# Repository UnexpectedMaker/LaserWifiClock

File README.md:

# Mod-able Laser Wifi Clock
Design files and code for my open source Mod-able RGB Laser Wifi Clock that I sell on tindie:
https://www.tindie.com/products/15501/

It's custom hardware and custom code but all open source so if you want the challenge of making one yourself or you want to hack the code, go for it!

I have a live stream build of the board here if you want to see what's involved:
https://www.youtube.com/watch?v=2W7_SHC2Mis

# Design Files
Inlcluded in this reposity:
- EagleCAD schematics and Board layout files (Eagle 9.2) 
- Exported Gerber files (Gerber 274X)
- STL & DXF files for the 3D printed case and laser cut pieces
- Adrduino code

# Assembling the case
Here is a video guide to assembling the case

https://youtu.be/fARj-D6XGP0

# Hacking the code
You will need to have the ESP8266 board for Arduino IDE installed. If you don't, you can follow the instructions here:
https://arduino-esp8266.readthedocs.io/en/2.5.0-beta2/installing.html

Once installed you'll need to select the *LOLIN(WEMOS) D1 R2 & Mini* as the board type.

Plus the following libraries from Library Manager
- One Button
- TimeLib
- WifiManager (tzapu)
- ArduinoJson

Enjoy!

# Support Unexpected Maker

I love designing, making and releasing our projects as open source. I do it because I believe it’s important to share knowledge and give back to the community, like many have done before me. It helps us all learn and grow.

That said, a lot of time, effort and finances have gone into designing and releasing these files, so please consider supporting me by buy some of my TiinyPICO products:

https://tinypico.com/shop

Or by buying one of our products on tindie:

https://www.tindie.com/stores/seonr/

Or by becoming a Patron:

https://www.patreon.com/unexpectedmaker

# Unexpected Maker
http://youtube.com/c/unexpectedmaker

http://twitter.com/unexpectedmaker

https://www.facebook.com/unexpectedmaker/

https://www.instagram.com/unexpectedmaker/

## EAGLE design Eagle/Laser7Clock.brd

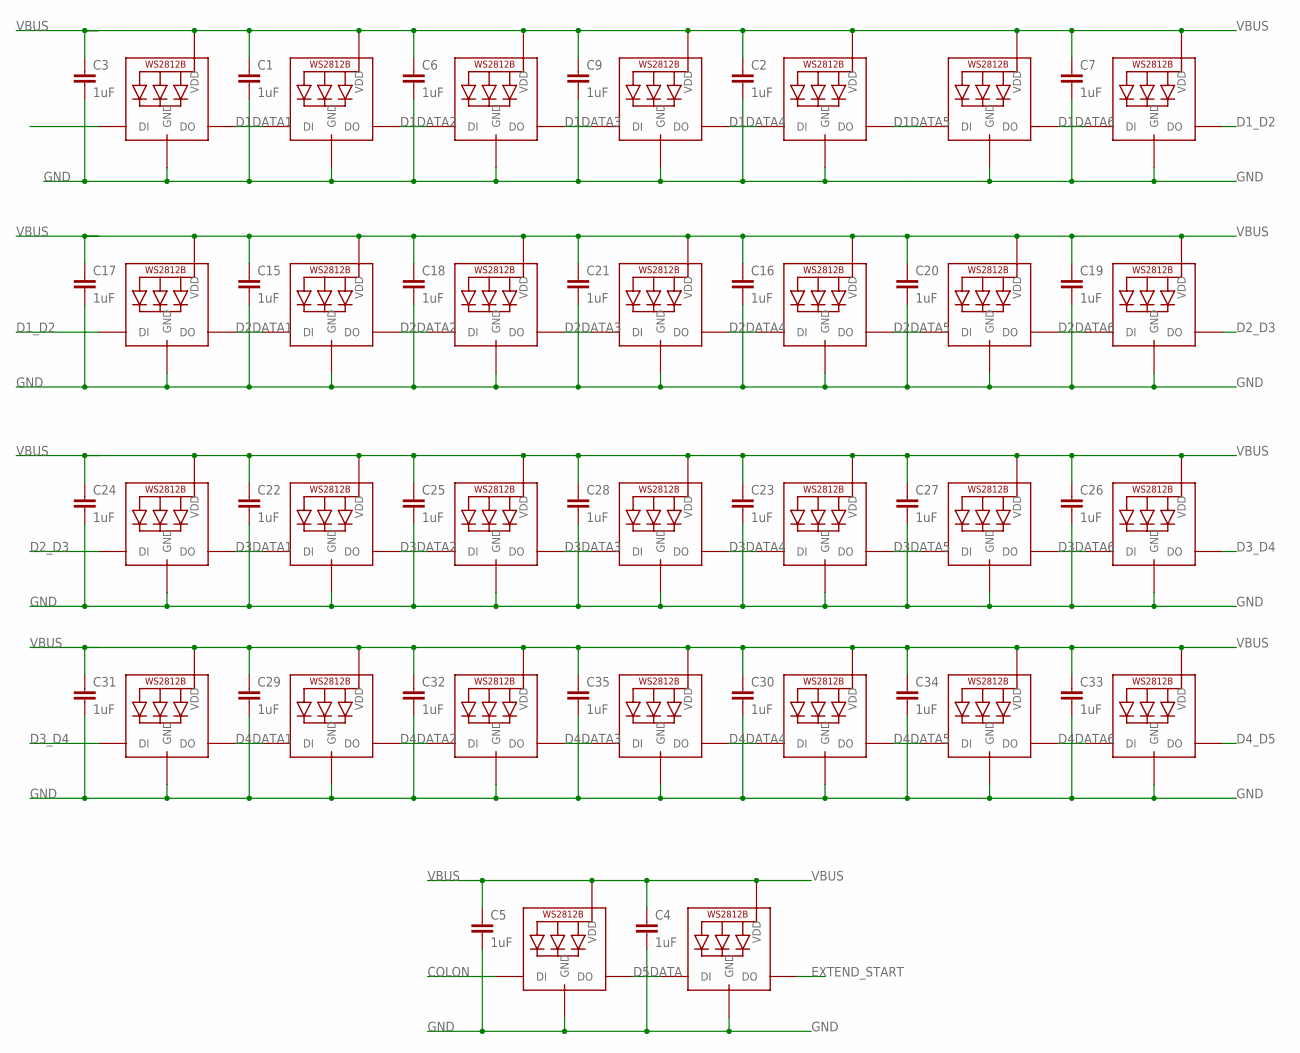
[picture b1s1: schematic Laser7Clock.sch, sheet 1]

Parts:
C1, C2, C3, C4, C5, C6, C7, C9, C15, C16, C17, C18, C19, C20, C21, C22, C23, C24, C25, C26, C27, C28, C29, C30, C31, C32, C33, C34, C35: 1uF; C0805K
D1L1, D1L2, D1L3, D1L4, D1L5, D1L6, D1L7, D2L1, D2L2, D2L3, D2L4, D2L5, D2L6, D2L7, D3L1, D3L2, D3L3, D3L4, D3L5, D3L6, D3L7, D4L1, D4L2, D4L3, D4L4, D4L5, D4L6, D4L7: WS2812B5050; WS2812B
LED1, LED2: WS2812B5050; WS2812B

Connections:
COLON: LED1.4-DIN (DI); also elsewhere on the board
D1DATA1: D1L1.2-DOUT (DO), D1L2.4-DIN (DI)
D1DATA2: D1L2.2-DOUT (DO), D1L3.4-DIN (DI)
D1DATA3: D1L3.2-DOUT (DO), D1L4.4-DIN (DI)
D1DATA4: D1L4.2-DOUT (DO), D1L5.4-DIN (DI)
D1DATA5: D1L5.2-DOUT (DO), D1L6.4-DIN (DI)
D1DATA6: D1L6.2-DOUT (DO), D1L7.4-DIN (DI)
D1_D2: D1L7.2-DOUT (DO), D2L1.4-DIN (DI)
D2DATA1: D2L1.2-DOUT (DO), D2L2.4-DIN (DI)
D2DATA2: D2L2.2-DOUT (DO), D2L3.4-DIN (DI)
D2DATA3: D2L3.2-DOUT (DO), D2L4.4-DIN (DI)
D2DATA4: D2L4.2-DOUT (DO), D2L5.4-DIN (DI)
D2DATA5: D2L5.2-DOUT (DO), D2L6.4-DIN (DI)
D2DATA6: D2L6.2-DOUT (DO), D2L7.4-DIN (DI)
D2_D3: D2L7.2-DOUT (DO), D3L1.4-DIN (DI)
D3DATA1: D3L1.2-DOUT (DO), D3L2.4-DIN (DI)
D3DATA2: D3L2.2-DOUT (DO), D3L3.4-DIN (DI)
D3DATA3: D3L3.2-DOUT (DO), D3L4.4-DIN (DI)
D3DATA4: D3L4.2-DOUT (DO), D3L5.4-DIN (DI)
D3DATA5: D3L5.2-DOUT (DO), D3L6.4-DIN (DI)
D3DATA6: D3L6.2-DOUT (DO), D3L7.4-DIN (DI)
D3_D4: D3L7.2-DOUT (DO), D4L1.4-DIN (DI)
D4DATA1: D4L1.2-DOUT (DO), D4L2.4-DIN (DI)
D4DATA2: D4L2.2-DOUT (DO), D4L3.4-DIN (DI)
D4DATA3: D4L3.2-DOUT (DO), D4L4.4-DIN (DI)
D4DATA4: D4L4.2-DOUT (DO), D4L5.4-DIN (DI)
D4DATA5: D4L5.2-DOUT (DO), D4L6.4-DIN (DI)
D4DATA6: D4L6.2-DOUT (DO), D4L7.4-DIN (DI)
D4_D5: D4L7.2-DOUT (DO); also elsewhere on the board
D5DATA: LED1.2-DOUT (DO), LED2.4-DIN (DI)
DI_R: D1L1.4-DIN (DI); also elsewhere on the board
EXTEND_START: LED2.2-DOUT (DO); also elsewhere on the board
GND: C1.2, C2.2, C3.2, C4.2, C5.2, C6.2, C7.2, C9.2, C15.2, C16.2, C17.2, C18.2, C19.2, C20.2, C21.2, C22.2, C23.2, C24.2, C25.2, C26.2, C27.2, C28.2, C29.2, C30.2, C31.2, C32.2, C33.2, C34.2, C35.2, D1L1.3-GND (GND), D1L2.3-GND (GND), D1L3.3-GND (GND), D1L4.3-GND (GND), D1L5.3-GND (GND), D1L6.3-GND (GND), D1L7.3-GND (GND), D2L1.3-GND (GND), D2L2.3-GND (GND), D2L3.3-GND (GND), D2L4.3-GND (GND), D2L5.3-GND (GND), D2L6.3-GND (GND), D2L7.3-GND (GND), D3L1.3-GND (GND), D3L2.3-GND (GND), D3L3.3-GND (GND), D3L4.3-GND (GND), D3L5.3-GND (GND), D3L6.3-GND (GND), D3L7.3-GND (GND), D4L1.3-GND (GND), D4L2.3-GND (GND), D4L3.3-GND (GND), D4L4.3-GND (GND), D4L5.3-GND (GND), D4L6.3-GND (GND), D4L7.3-GND (GND), LED1.3-GND (GND), LED2.3-GND (GND); also elsewhere on the board
VBUS: C1.1, C2.1, C3.1, C4.1, C5.1, C6.1, C7.1, C9.1, C15.1, C16.1, C17.1, C18.1, C19.1, C20.1, C21.1, C22.1, C23.1, C24.1, C25.1, C26.1, C27.1, C28.1, C29.1, C30.1, C31.1, C32.1, C33.1, C34.1, C35.1, D1L1.1-VDD (VDD), D1L2.1-VDD (VDD), D1L3.1-VDD (VDD), D1L4.1-VDD (VDD), D1L5.1-VDD (VDD), D1L6.1-VDD (VDD), D1L7.1-VDD (VDD), D2L1.1-VDD (VDD), D2L2.1-VDD (VDD), D2L3.1-VDD (VDD), D2L4.1-VDD (VDD), D2L5.1-VDD (VDD), D2L6.1-VDD (VDD), D2L7.1-VDD (VDD), D3L1.1-VDD (VDD), D3L2.1-VDD (VDD), D3L3.1-VDD (VDD), D3L4.1-VDD (VDD), D3L5.1-VDD (VDD), D3L6.1-VDD (VDD), D3L7.1-VDD (VDD), D4L1.1-VDD (VDD), D4L2.1-VDD (VDD), D4L3.1-VDD (VDD), D4L4.1-VDD (VDD), D4L5.1-VDD (VDD), D4L6.1-VDD (VDD), D4L7.1-VDD (VDD), LED1.1-VDD (VDD), LED2.1-VDD (VDD); also elsewhere on the board

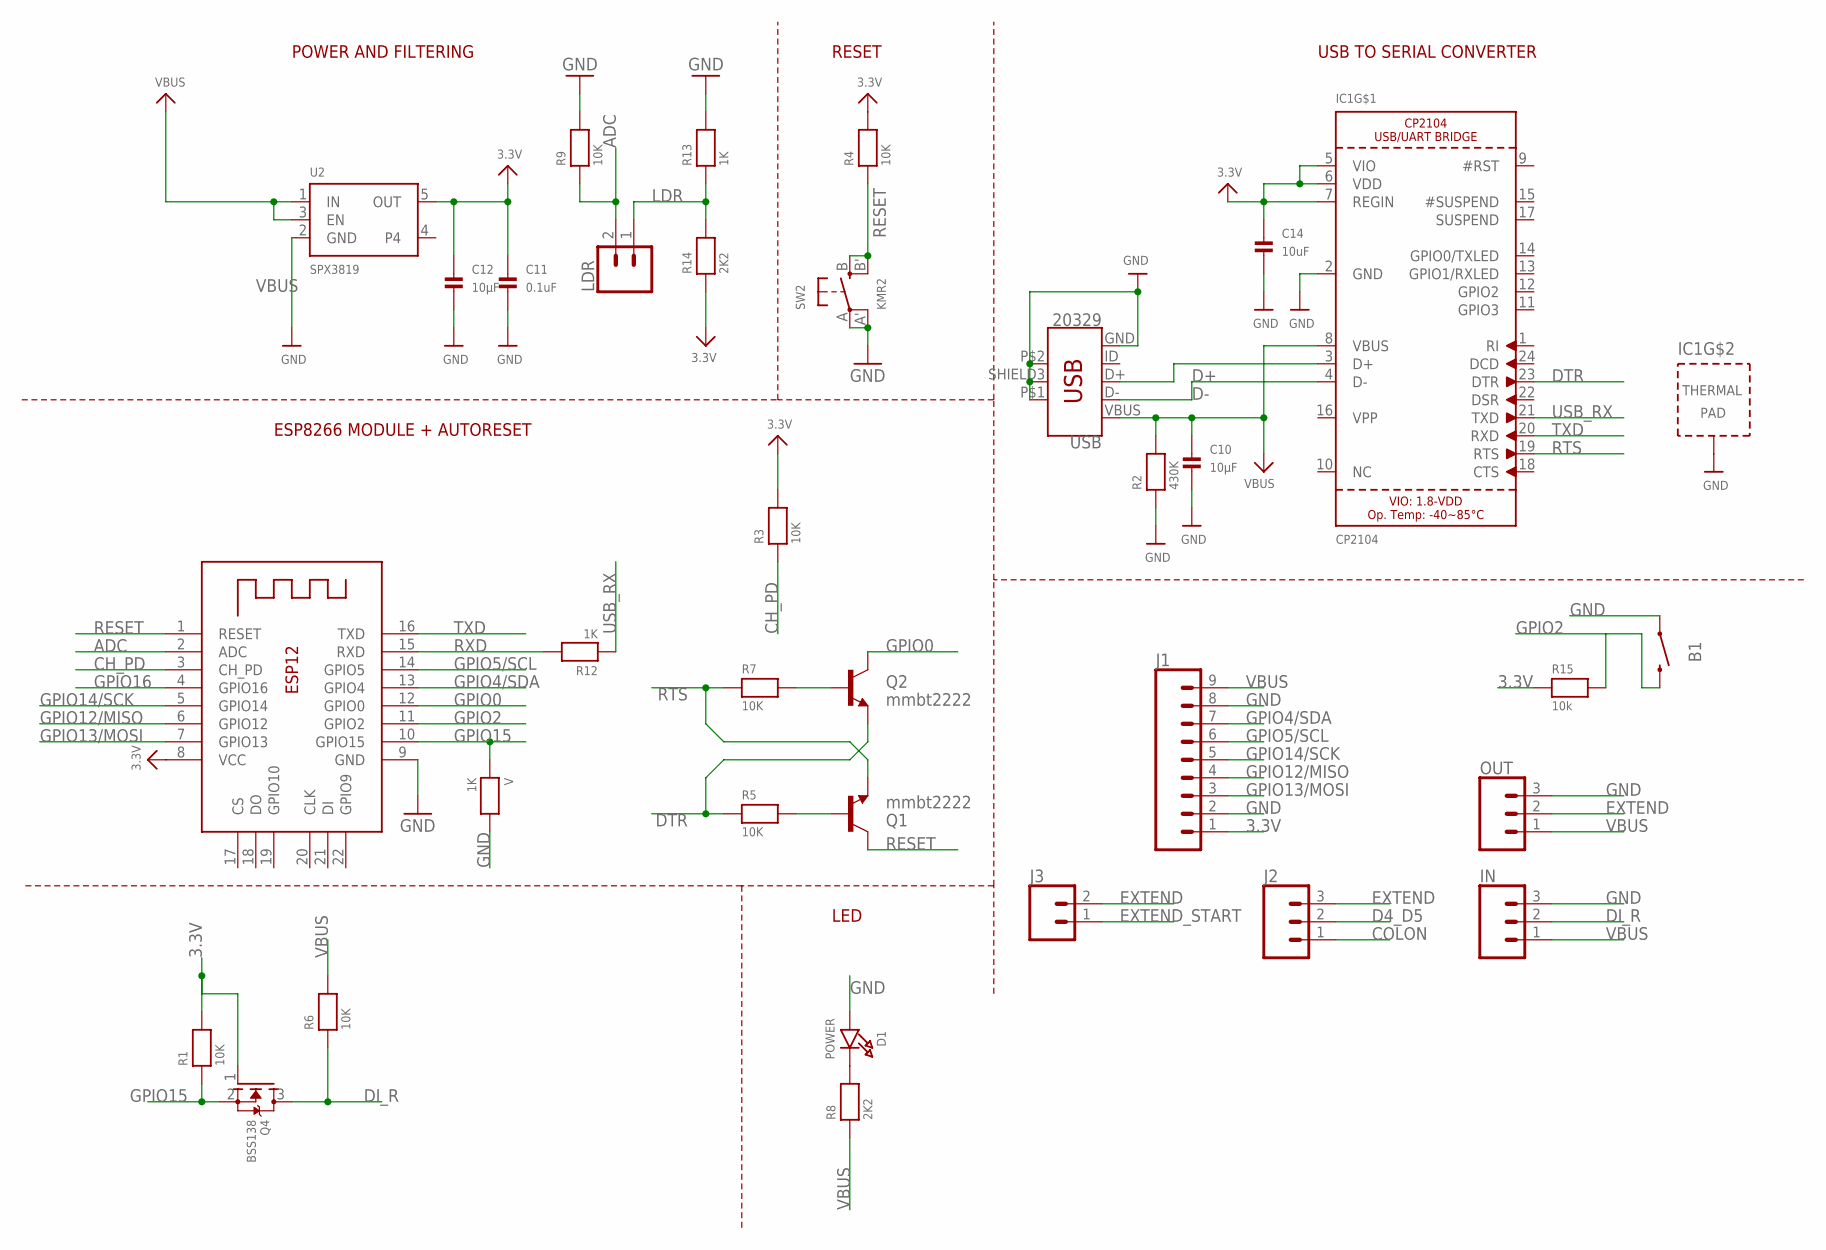
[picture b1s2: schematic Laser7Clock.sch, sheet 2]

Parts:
B1: MOMENTARY-SWITCH-SPST-PTH-RIGHT-ANGLE-KIT; TACTILE_SWITCH_PTH_RIGHT_ANGLE_KIT
C10, C12: 10µF; _0805MP
C11: 0.1uF; _0805MP
C14: 10uF; _0805MP
D1: POWER; CHIPLED_0805_NOOUTLINE
IC1: CP2104; QFN24_4MM_SMSC
IN: CONN_03LONGPADS; 1X03_LONGPADS
J1: CONN_09NO_SILK; 1X09_NO_SILK
J2: CONN_031X03_NO_SILK; 1X03_NO_SILK
J3: CONN_021X02_NO_SILK; 1X02_NO_SILK
LDR: CONN_021X02_NO_SILK; 1X02_NO_SILK
OUT: CONN_03LONGPADS; 1X03_LONGPADS
Q1, Q2: mmbt2222; SOT23-3
Q4: BSS138; SOT23-R
R1, R3, R4, R5, R6, R7: 10K; _0603MP
R2: 430K; _0805MP
R8, R14: 2K2; _0805MP
R9: 10K; _0805MP
R12: 1K; _0603MP
R13: 1K; _0805MP
R15: 10k; _0603MP
SW2: KMR2; BTN_KMR2_4.6X2.8
U2: SPX3819; SOT23-5
USB: 20329; USB-B-MICRO-SMD
V: 1K; _0603MP
X2: ESP-12; ESP-12E

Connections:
3.3V: C11.1, C12.1, C14.1, IC1.5 (VIO), IC1.6 (VDD), IC1.7 (REGIN), J1.1, Q4.1 (G), R1.2, R3.2, R4.2, R14.1, R15.1, U2.5 (OUT), X2.8 (VCC)
ADC: LDR.2, R9.1, X2.2 (ADC)
CH_PD: R3.1, X2.3 (CH_PD)
COLON: J2.1; also elsewhere on the board
D4_D5: J2.2; also elsewhere on the board
D+: IC1.3 (D+), USB.D+
D-: IC1.4 (D-), USB.D-
DI_R: IN.2, Q4.3 (D), R6.1; also elsewhere on the board
DTR: IC1.23 (DTR), Q2.2 (E), R5.1
EXTEND: J2.3, J3.2, OUT.2
EXTEND_START: J3.1; also elsewhere on the board
GND: B1.1, C10.2, C11.2, C12.2, C14.2, D1.A, IC1.2 (GND), IC1.THERM (TP), IN.3, J1.2, J1.8, OUT.3, R2.1, R9.2, R13.2, SW2.A, SW2.A' (P1), U2.2 (GND), USB.GND, USB.P$1 (SHIELD1), USB.P$2 (SHIELD2), USB.SHIELD3 (SHIELD), V.2, X2.9 (GND); also elsewhere on the board
GPIO0: Q2.3 (C), X2.12 (GPIO0)
GPIO2: B1.2, R15.2, X2.11 (GPIO2)
GPIO4/SDA: J1.7, X2.13 (GPIO4)
GPIO5/SCL: J1.6, X2.14 (GPIO5)
GPIO12/MISO: J1.4, X2.6 (GPIO12)
GPIO13/MOSI: J1.3, X2.7 (GPIO13)
GPIO14/SCK: J1.5, X2.5 (GPIO14)
GPIO15: Q4.2 (S), R1.1, V.1, X2.10 (GPIO15)
GPIO16: X2.4 (GPIO16)
LDR: LDR.1, R13.1, R14.2
unnamed: D1.C, R8.2
unnamed: Q1.1 (B), R5.2
unnamed: Q2.1 (B), R7.2
RESET: Q1.3 (C), R4.1, SW2.B (S), SW2.B' (S1), X2.1 (RESET)
RTS: IC1.19 (RTS), Q1.2 (E), R7.1
RXD: R12.2, X2.15 (RXD)
TXD: IC1.20 (RXD), X2.16 (TXD)
USB_RX: IC1.21 (TXD), R12.1
VBUS: C10.1, IC1.8 (VBUS), IN.1, J1.9, OUT.1, R2.2, R6.2, R8.1, U2.1 (IN), U2.3 (EN), USB.VBUS; also elsewhere on the board

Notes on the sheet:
POWER AND FILTERING
RESET
USB TO SERIAL CONVERTER
LED
ESP8266 MODULE + AUTORESET

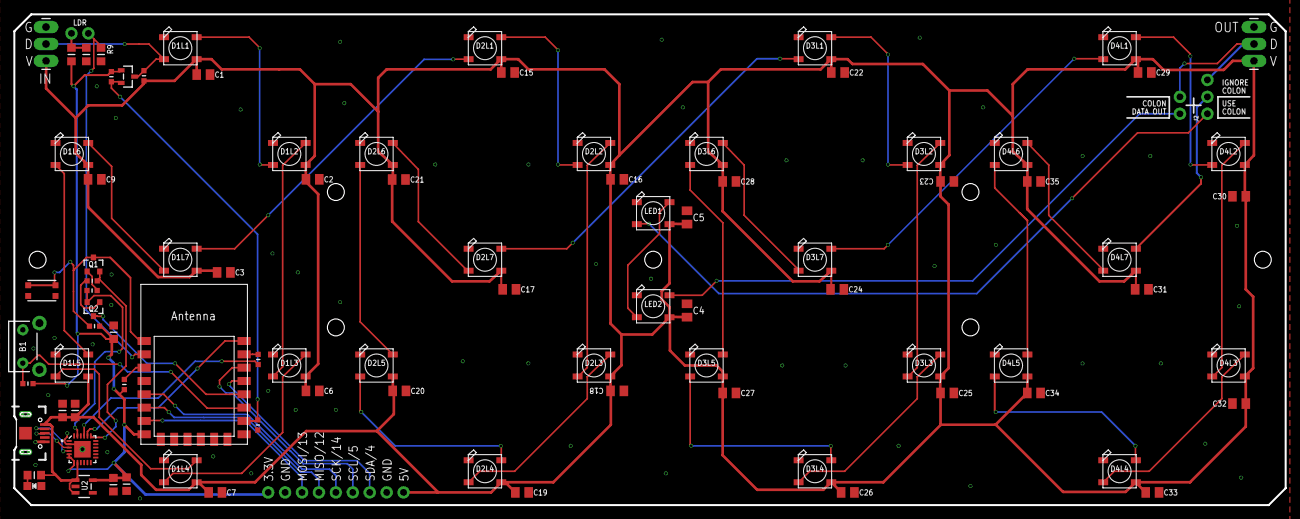
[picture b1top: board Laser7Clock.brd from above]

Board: 2 copper layers, 190.8 x 73.7 mm, 93 parts (0 on the bottom side), 58 nets.

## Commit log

2019-01-14 Initial commit... more to come!
2019-02-01 Addition of Arduino code
2019-02-01 Added Arduino code
2019-02-01 Updated acrylic DFX files
2019-02-01 Added missing colon segment design & renamed digit segment file

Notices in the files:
parts and their libraries:
SparkFun-Connectors: Licensing: Creative Commons ShareAlike 4.0 International - https://creativecommons.org/licenses/by-sa/4.0
microbuilder: This work is placed in the public domain, and may be freely used for commercial and non-commercial work with the following conditions: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
